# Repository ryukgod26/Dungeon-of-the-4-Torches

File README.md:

# Dungeon of 4 Torches

## Introduction 
This is a Puzzle Game. There are 4 Doors: North Door, West Door, East Door, North Door. The North has a Boss Enemy Behind t and is Locked. You Will need to collect One Key From every other Room to unlock the North Room. Every Door has as Challenge behind it. One Door has a Puzzle where you will have to push a block to a empty space, one room has Slimes and you will have to kill them to get the key and one room you will have to dodge the traps and get the key. This game is in very Early Phase right now because I created this Game in a rush in like 2-3 days. From Now On (3rd feb 2026) i will Start Poliushing this Game.

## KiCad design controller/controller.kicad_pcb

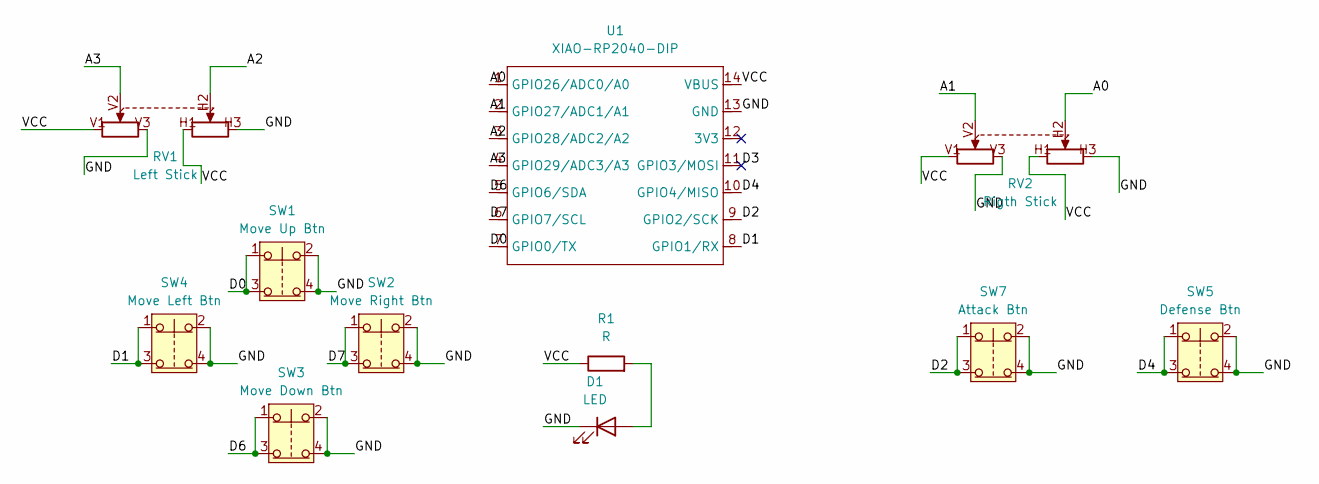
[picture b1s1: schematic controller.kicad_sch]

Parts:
D1: LED; LED_D5.0mm
R1: R; R_Axial_DIN0207_L6.3mm_D2.5mm_P10.16mm_Horizontal
RV1: Left Stick; XDCR_COM-09032
RV2: Rigth Stick; XDCR_COM-09032
SW1: Move Up Btn; Push_E-Switch_KS01Q01
SW2: Move Right Btn; Push_E-Switch_KS01Q01
SW3: Move Down Btn; Push_E-Switch_KS01Q01
SW4: Move Left Btn; Push_E-Switch_KS01Q01
SW5: Defense Btn; Push_E-Switch_KS01Q01
SW7: Attack Btn; Push_E-Switch_KS01Q01
U1: XIAO-RP2040-DIP

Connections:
/A0: RV2.H2 (5), U1.1 (GPIO26/ADC0/A0)
/A1: RV2.V2 (2), U1.2 (GPIO27/ADC1/A1)
/A2: RV1.H2 (5), U1.3 (GPIO28/ADC2/A2)
/A3: RV1.V2 (2), U1.4 (GPIO29/ADC3/A3)
/D0: SW1.1, SW1.3, U1.7 (GPIO0/TX)
/D1: SW4.1, SW4.3, U1.8 (GPIO1/RX)
/D2: SW7.1, SW7.3, U1.9 (GPIO2/SCK)
/D3: U1.11 (GPIO3/MOSI)
/D3_1: U1.11 (GPIO3/MOSI)
/D4: SW5.1, SW5.3, U1.10 (GPIO4/MISO)
/D6: SW3.1, SW3.3, U1.5 (GPIO6/SDA)
/D7: SW2.1, SW2.3, U1.6 (GPIO7/SCL)
/GND: D1.1 (K), RV1.H3 (6), RV1.V3 (3), RV2.H3 (6), RV2.V3 (3), SW1.2, SW1.4, SW2.2, SW2.4, SW3.2, SW3.4, SW4.2, SW4.4, SW5.2, SW5.4, SW7.2, SW7.4, U1.13 (GND)
/VCC: R1.1, RV1.H1 (4), RV1.V1 (1), RV2.H1 (4), RV2.V1 (1), U1.14 (VBUS)
unnamed: D1.2 (A), R1.2

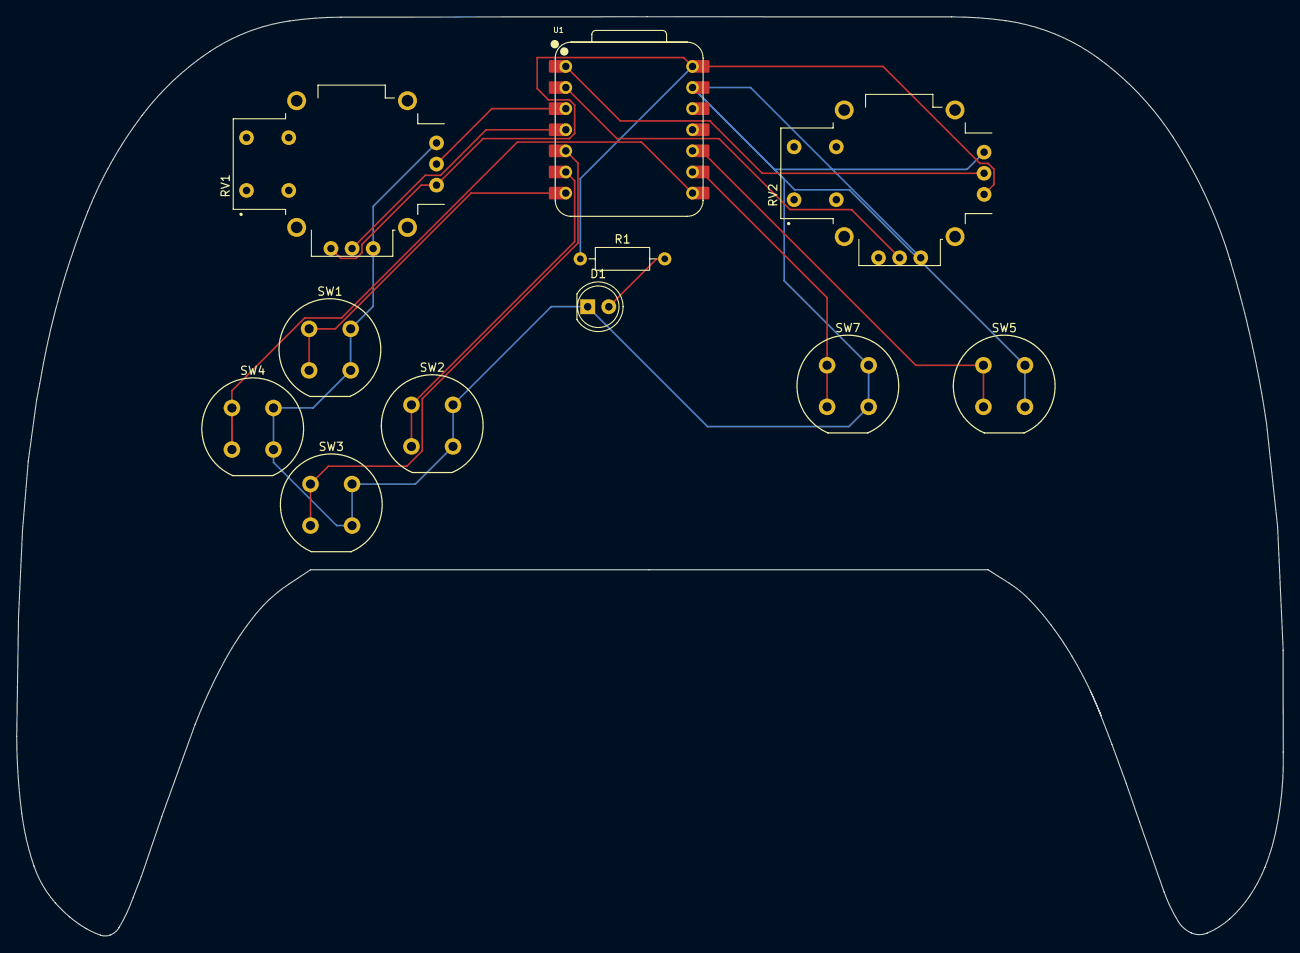
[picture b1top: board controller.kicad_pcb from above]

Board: 2 copper layers, 152.4 x 110.6 mm, 11 parts (0 on the bottom side), 13 nets.

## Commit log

2026-01-06 Intiall Commit
2026-01-07 Add new sprite assets and update project configuration
    - Added new idle and run sprite images for the player character:
    - idle_right.png
    - idle_up.png
    - run_down.png
    - run_left.png
    - run_right.png
2026-01-08 Add new enemy sprites and tilesets for dungeon environment
    - Introduced new enemy sprites including various types of orcs, goblins, and undead creatures.
    - Added corresponding metadata files for texture compression and import settings.
    - Included new tilesets for dungeon decoration, including various floor types, walls, and traps.
    - Updated project configuration to include new main scene and autoload scripts for global variables.
2026-01-09 Fixed the Attack Animation Bug Added Damage For Attacks which means Player Can now Damage ands kill Enemies ShapeCast2D now Perfectly alligns with Player Created Two New States Death and Hurt. Added 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
2026-01-10 Update health system and add health bar UI; fix spike activation logic
2026-01-11 Add animated bronze key frames and update project configuration
    - Added new animated frames for the bronze key (frames 25 to 30) in the Pixel Art Key Pack.
    - Updated the import settings for each new frame to ensure proper texture compression and metadata.
    - Modified the tileset import settings to reflect a new UID.
    - Changed the main scene UID in the project configuration to point to the updated main scene.
2026-01-12 Add Camera2D nodes to dungeon scenes and update player health logic
2026-01-17 Created the Basic Schematic and PCB for the COntroller
2026-01-18 So I solved all the errors I was getting in the kicad. Now Schematics are all done. All Which is left is PCB. WHich WIll be done in few hours. I have Changed all the Buttons I used for hackpad to Ope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
2026-01-19 SO I have Started and finsihed the PCb. I had to assign all the footprint to all the components in the schematic editor. Then After Importing them I had to import a Graphic Picture of Controller Outl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
2026-01-24 Add Wakatime integration plugin for Godot
    - Introduced a new Wakatime plugin to track coding time within the Godot editor.
    - Added UI components for API key input and a counter to display coding time.
    - Implemented functionality to download and manage Wakatime CLI and decompressor.
    - Created utility functions for platform detection and configuration file management.
    - Included icons and images for the plugin interface.
    - Configured project settings to enable the Wakatime plugin.
2026-02-28 Add main menu scene, enable Y sorting for entities, and update player script
    - Created a new main menu scene with Play, Options, and Quit buttons.
    - Enabled Y sorting for the Entities node in the main game scene to improve rendering order.
    - Cleaned up the player script by removing unnecessary blank lines and ensuring proper functionality.
    - Added various image import configurations for the OPL Kicad Library assets.
2026-02-28 Add main menu scene and implement button functionality
2026-03-01 Refactor main menu by removing options button and its functionality; add pause menu scene and implement pause functionality
2026-03-01 Add new font assets and import configurations for Nexa and Roboto families
    - Added Nexa-ExtraLight and Nexa-Heavy font files along with their import configurations.
    - Introduced multiple Roboto font styles including Black, BlackItalic, Bold, BoldCondensed, BoldCondensedItalic, BoldItalic, Condensed, Light, Medium, Regular, Thin, and their respective italic varia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
    - Included a Roboto specimen PDF for reference.
    - Added a NOTICE.txt file for Roboto font usage permissions.
2026-03-10 Update boss enemy script and main menu assets; add new boss2 script, update main menu scene with styles and images, and adjust pause menu animations.
2026-03-10 Update boss and slime enemy scripts; set motion mode for boss, slime, and player, and adjust export path for web build.
